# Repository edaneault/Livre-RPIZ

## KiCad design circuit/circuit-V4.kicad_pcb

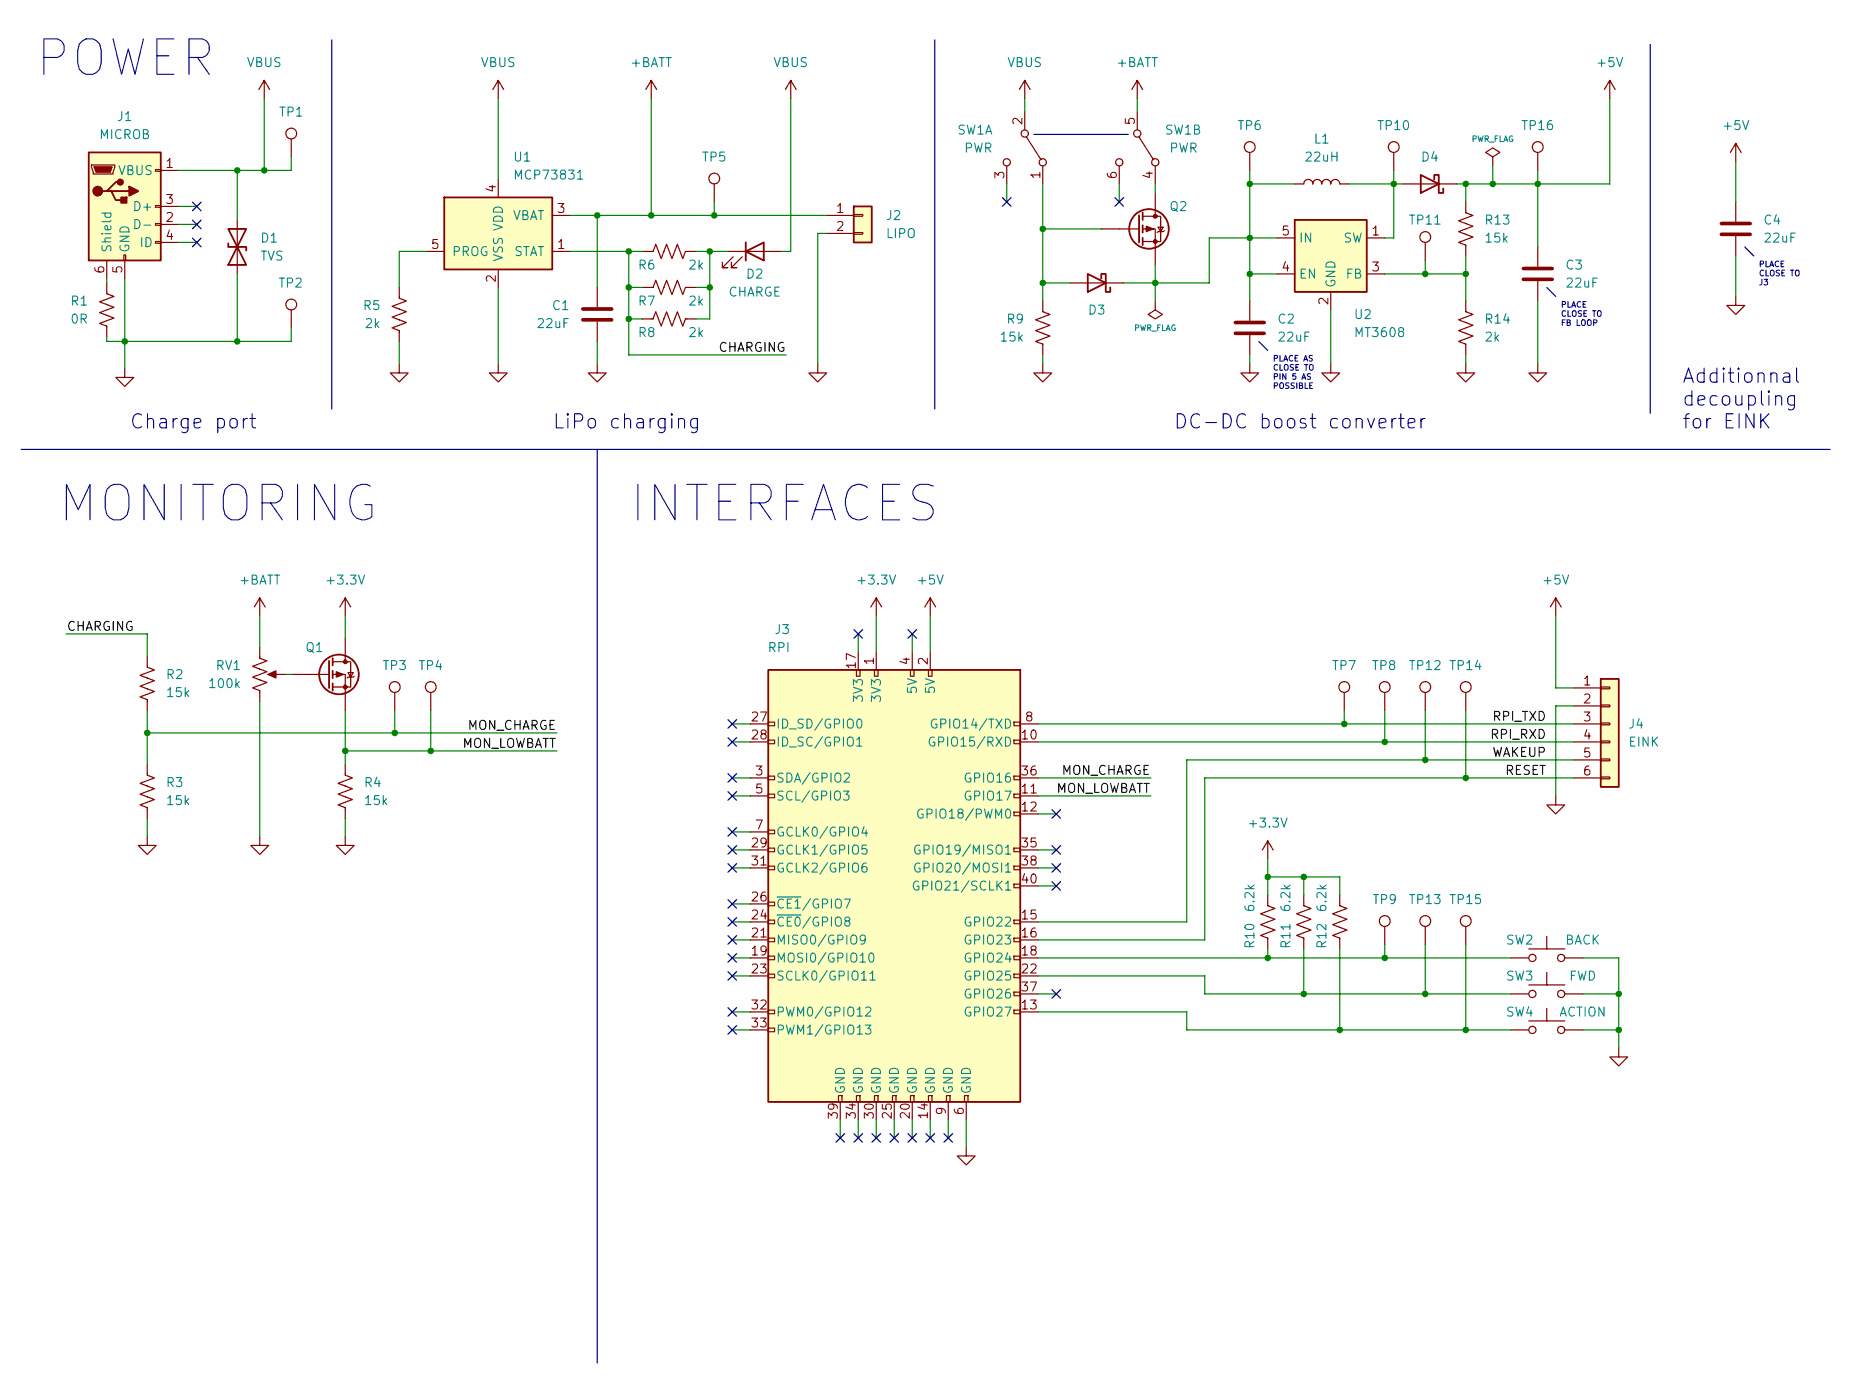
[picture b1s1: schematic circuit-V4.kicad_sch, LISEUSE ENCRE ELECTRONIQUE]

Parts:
C1, C2, C3, C4: 22uF; CP_EIA-3528-21_Kemet-B_Pad1.50x2.35mm_HandSolder; MfgPartNo TAJB226K020RNJ
D1: TVS; R_0603_1608Metric_Pad0.98x0.95mm_HandSolder; MfgPartNo EGA10603V12B0DG
D2: CHARGE; D_WURTH_3538; MfgPartNo 150141GS73100
D3, D4: D_SMC_FAIRCHILD; MfgPartNo SS34
J1: MICROB; USB_Micro-B_Amphenol_10118194_Horizontal; MfgPartNo 10118194-0001LF
J2: LIPO; JST_PH_S2B-PH-K_1x02_P2.00mm_Horizontal; MfgPartNo S2B-PH-K-S
J3: RPI; PinHeader_2x20_P2.54mm_Vertical; MfgPartNo PPTC202LFBN-RC
J4: EINK; JST_XH_S6B-XH-SM4-TB; MfgPartNo S6B-XH-SM4-TB
L1: 22uH; L_TaiTech_TMPC1004; MfgPartNo TPMC 1004H-220MG-D
Q1, Q2: SOT23_DIODESINC; MfgPartNo DMP2045U
R1: 0R; R_1206_3216Metric_Pad1.30x1.75mm_HandSolder; MfgPartNo NONE
R2, R3, R4, R9, R13: 15k; R_1206_3216Metric_Pad1.30x1.75mm_HandSolder; MfgPartNo RMCF1206FT15K0
R5, R6, R7, R8, R14: 2k; R_1206_3216Metric_Pad1.30x1.75mm_HandSolder; MfgPartNo RMCF1206FG2K00
R10, R11, R12: 6.2k; R_1206_3216Metric_Pad1.30x1.75mm_HandSolder; MfgPartNo RMCF1206JT6K20
RV1: 100k; Potentiometer_Bourns_TC33X_Vertical; MfgPartNo TC33X-2-104E
SW1: PWR; SLW-108645; MfgPartNo SLW-108645-4A-RA-D
SW2: BACK; SW_SPST_PTS815; MfgPartNo PTS815 SJM 250 SMTR LFS
SW3: FWD; SW_SPST_PTS815; MfgPartNo PTS815 SJM 250 SMTR LFS
SW4: ACTION; SW_SPST_PTS815; MfgPartNo PTS815 SJM 250 SMTR LFS
TP1, TP2, TP5, TP16: TestPoint_Pad_D2.5mm; MfgPartNo NONE
TP3, TP4, TP6, TP7, TP8, TP9, TP10, TP11, TP12, TP13, TP14, TP15: TestPoint_Pad_D1.5mm; MfgPartNo NONE
U1: MCP73831; SOT-23-5; MfgPartNo MCP73831T-2ACI/OT
U2: MT3608; SOT-23-6; MfgPartNo MT3608

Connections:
+3.3V: J3.1 (3V3), Q1.1 (D), R10.1, R11.1, R12.1
+5V: C3.1, C4.1, D4.1 (K), J3.2 (5V), J4.1, R13.1, TP16.1
+BATT: C1.1, J2.1, RV1.1, SW1.5 (B), TP5.1, U1.3 (VBAT)
/CHARGING: R2.1, R6.2, R7.2, R8.2, U1.1 (STAT)
/MON_CHARGE: J3.36 (GPIO16), R2.2, R3.1, TP3.1
/MON_LOWBATT: J3.11 (GPIO17), Q1.3 (S), R4.1, TP4.1
/RESET: J3.16 (GPIO23), J4.6, TP14.1
/RPI_RXD: J3.10 (GPIO15/RXD), J4.4, TP8.1
/RPI_TXD: J3.8 (GPIO14/TXD), J4.3, TP7.1
/WAKEUP: J3.15 (GPIO22), J4.5, TP12.1
GND: C1.2, C2.2, C3.2, C4.2, D1.1 (A1), J1.5 (GND), J2.2, J3.6 (GND), J4.2, R1.2, R3.2, R4.2, R5.2, R9.2, R14.2, RV1.3, SW2.2, SW3.2, SW4.2, TP2.1, U1.2 (VSS), U2.2 (GND)
unnamed: C2.1, D3.1 (K), L1.1, Q2.3 (S), TP6.1, U2.4 (EN), U2.5 (IN)
unnamed: D2.1 (K), R6.1, R7.1, R8.1
unnamed: D3.2 (A), Q2.2 (G), R9.1, SW1.1 (A)
unnamed: D4.2 (A), L1.2, TP10.1, U2.1 (SW)
unnamed: J1.6 (Shield), R1.1
unnamed: J3.13 (GPIO27), R12.2, SW4.1, TP15.1
unnamed: J3.18 (GPIO24), R10.2, SW2.1, TP9.1
unnamed: J3.22 (GPIO25), R11.2, SW3.1, TP13.1
unnamed: Q1.2 (G), RV1.2
unnamed: Q2.1 (D), SW1.4 (A)
unnamed: R5.1, U1.5 (PROG)
unnamed: R13.2, R14.1, TP11.1, U2.3 (FB)
VBUS: D1.2 (A2), D2.2 (A), J1.1 (VBUS), SW1.2 (B), TP1.1, U1.4 (VDD)

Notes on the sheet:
PLACE AS CLOSE TO PIN 5 AS POSSIBLE
INTERFACES
DC-DC boost converter
MONITORING
POWER
LiPo charging
PLACE CLOSE TO J3
Additionnal decoupling for EINK
Charge port
PLACE CLOSE TO FB LOOP

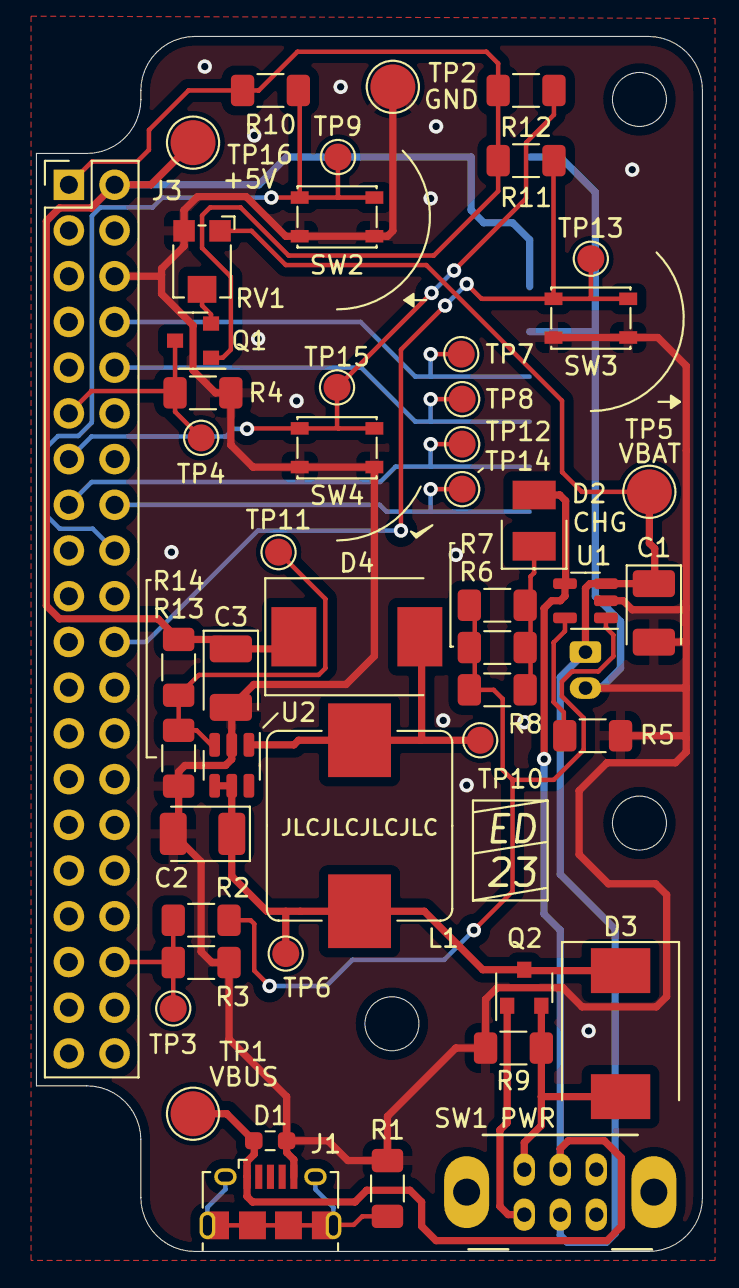
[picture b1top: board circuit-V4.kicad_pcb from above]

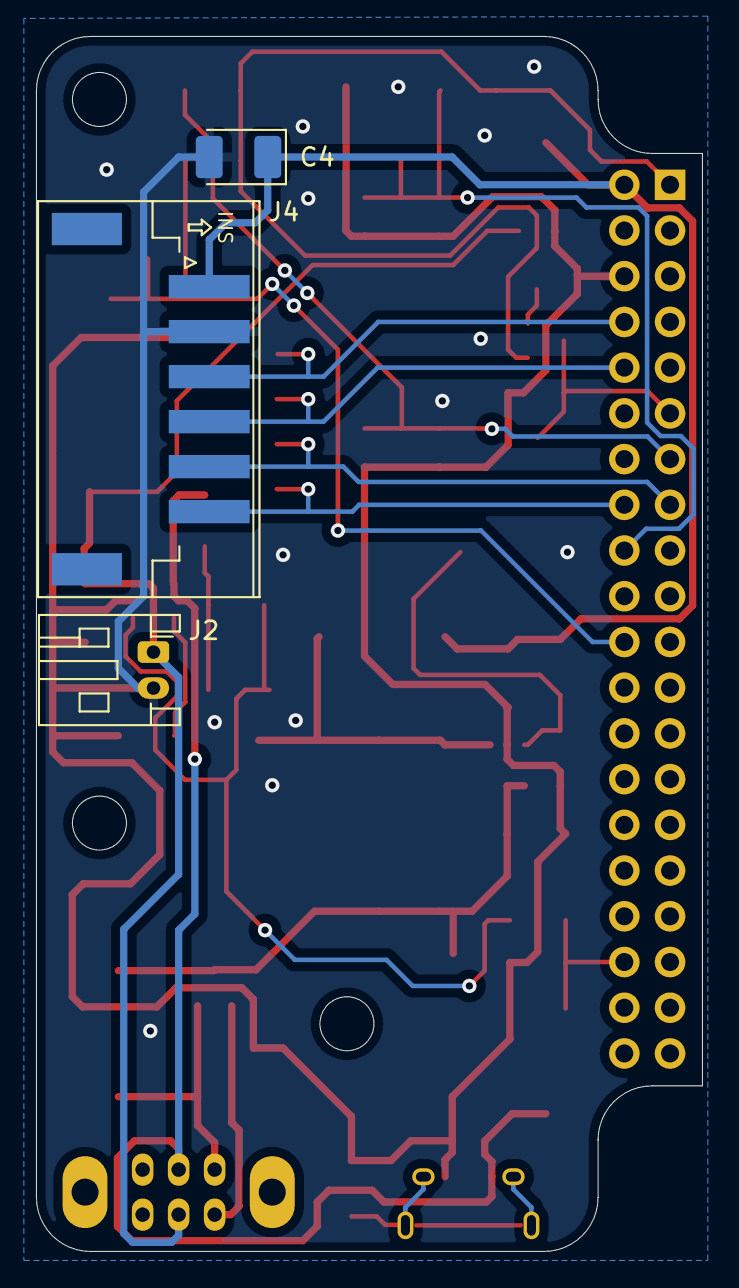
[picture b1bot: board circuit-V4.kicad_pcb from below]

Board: 2 copper layers, 37.0 x 67.5 mm, 52 parts (3 on the bottom side), 24 nets.

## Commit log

2024-03-27 Import massif du projet en date du 20 novembre 2023
